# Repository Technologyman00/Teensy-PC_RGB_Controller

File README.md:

# Teensy-PC_RGB_Controller
 
The whole Idea behind this project was to create a much better RGB controller than the controllers or motherboard software I have seen. Currently It has already met that goal as it can play any pattern for many LEDs and up to individual 40 devices. I am still working on the user interface and many qualities of life things, but the main functionality does work. HOWEVER, it will need a PCB made to power all the LEDs as a Teensy cannot power that many safely.

## Features

- No Extra load on the CPU. The teensy has its own built in CPU that will handle all the commands to the ARGB devices.
- Store Loads of Patterns or Huge animations. The teensy uses an SD card to save and read all the patterns allowing for a huge number of patterns to be saved.
- Up to 40 ports. Most Controllers top out at a maximum of 4 ports. The teensy has 40! This allows each device to do its own individual pattern.
- Any pattern! There are no limitations on what can be displayed because it plays back frames allowing an almost infinite amount of customization. 
- Standard Plugs! This uses the regular 3 pin 5V ARGB connectors so any device with the same connector can be used!
- OPEN SOURCE! Are you a bit handier than most? You can change anything you would ever what about this project!

## Documentation
### Pattern Files

Description | Command | Argument 1 | Argument 2
------------ | -------------| ------------ | -------------|
Send RGB Command: | 0 | Port Number | Color Data |
Send HSV Command: | 1 | Port Number | Hue (2 Bytes) S (1 Byte) V (1 Byte)|
Change Frame Delay: | 2 | Delay (2 Bytes) | N/A |
Create Device/Change Length: | 3 | Port Number | Number of Pixels |
Start New Frame: | 4 | N/A | N/A | N/A |

- Port 13 is not accessable from the hardware as it has the status LED so it was intentionally skipped in the PCB design. 

- Color Data is a continuous set of the RGB or HSV values. It will be (3 * Number of Pixels in Device) bytes long. For example it would go (Red Byte)(Blue Byte)(Green Byte)(Red Byte)(Blue Byte)(Green Byte)... or (Hue Byte)(Saturation Byte)(Value Byte)(Hue Byte)(Saturation Byte)(Value Byte)... All these bytes are from 0-255 with no decimals, as bytes are. For hue, saturation, and value these are all scaled to their corrective values.

- The delay value is split into 2 different bytes to allow a delay between 0 and 65535ms or 65.5 seconds. This allows a great range between quick animations and still colors. This value does not matter so much for still colors as the pattern file will just start over once it reaches the end re-displaying the same color.

### Serial Commands

Description | Command | Argument 1 | Argument 2 | Argument 3 |
------------ | -------------| ------------ | -------------| -------------|
Play File on SD Card: | P | File Name | N/A | N/A |
Write File to SD Card: | W | File Name | Length to Read (4 Bytes) | File Data |
Delete File on SD Card: | X | File Name | N/A | N/A |
List Files on SD Card: | L | N/A | N/A | N/A |
Change Startup File: | S | File Name | N/A | N/A |
Display Frame: | D | RGB or HSV -> (0 or 1) | Port Number | Color Data |
New Device: | N | Port | Number of Pixels | N/A |
Restart Teensy: | R | N/A | N/A | N/A |
Check Teensy Tempature: | T | N/A | N/A | N/A |

- File Name requires the file type *"example.txt"*
- File Data follows the documentation as setup in pattern files
- Length to Read is split into 4 bytes to allow very large files to be transferred (~4.3 GB) (if larger than ~4.3 GB just put the file onto the SD card manually)
- Color Data also follows the documentation as shown in pattern files
- ***Deleting files will ask if "Are sure you want to delete this?" A response is needed of Y/N before it will continue. Everything is halted when this is prompted.***
- ***Showing a Frame will not return to normal file reading until an exit command of X is sent.***

### Startup Handler

On startup the teensy will first read the *startup.txt* file which should contain the name of the file and only the name of the file. If this file does not exist or the code is unhappy with what was entered it will delete the *startup.txt* file and replace it with a *startup.txt* file that will run the default pattern file. The default pattern file sets all 40 ports to display Green on 255 pixels on those ports. This should make it so that it is obvious that the Teensy is working. The *startup.txt* file can be changed by either editing the file in a text editor or by sending the S command over serial.

## Updates
6/6
Full Deployment!!!!!
Example 1: https://youtu.be/utrNA2Hu2Kg
Example 2: https://youtu.be/6SqUPKUgLiA

5/30 Version 2 of the PCB was ordered and should be arriving shortly. This new version is to fix the concerns with the previous version, as the size was quite large and there was a design error. Both should be fixed in this version. Pin 13 was also taken off of the available pins as it was decided that it should be used as a status LED and should remain off if used. 

3/14 PCB Came in had issues. The Output enable pin was grounded not powered, which means it was disabled not enabled. (Woops) A small soldered wire fixed that. 
First Test : https://youtu.be/IeGvDfm8C_M

## Limitations
#### Files
   - Limited to a File Name of 8 Characters
     - example1.txt is at the max length
   - Is not case-sensitive 
     - example1.txt == EXAMPLE1.txt
      
#### Max SD card size is 32 GB
   - There are some potential work arounds for larger SD cards
   
#### LED Devices can only be added not removed per a given reboot
   - I really cant imagine this being an issue for anyone, but I thought its important to note just incase.
   - If 40 devices are created then they cannot be removed until a reboot
   - All 40 devices will be written to until a reboot occurs

## To Do
- [ ] Create Pattern Designer
- [ ] Loop Commands inside Files?
- [ ] Command Files for other Files?
- [ ] Allow devices to be removed without reboot?

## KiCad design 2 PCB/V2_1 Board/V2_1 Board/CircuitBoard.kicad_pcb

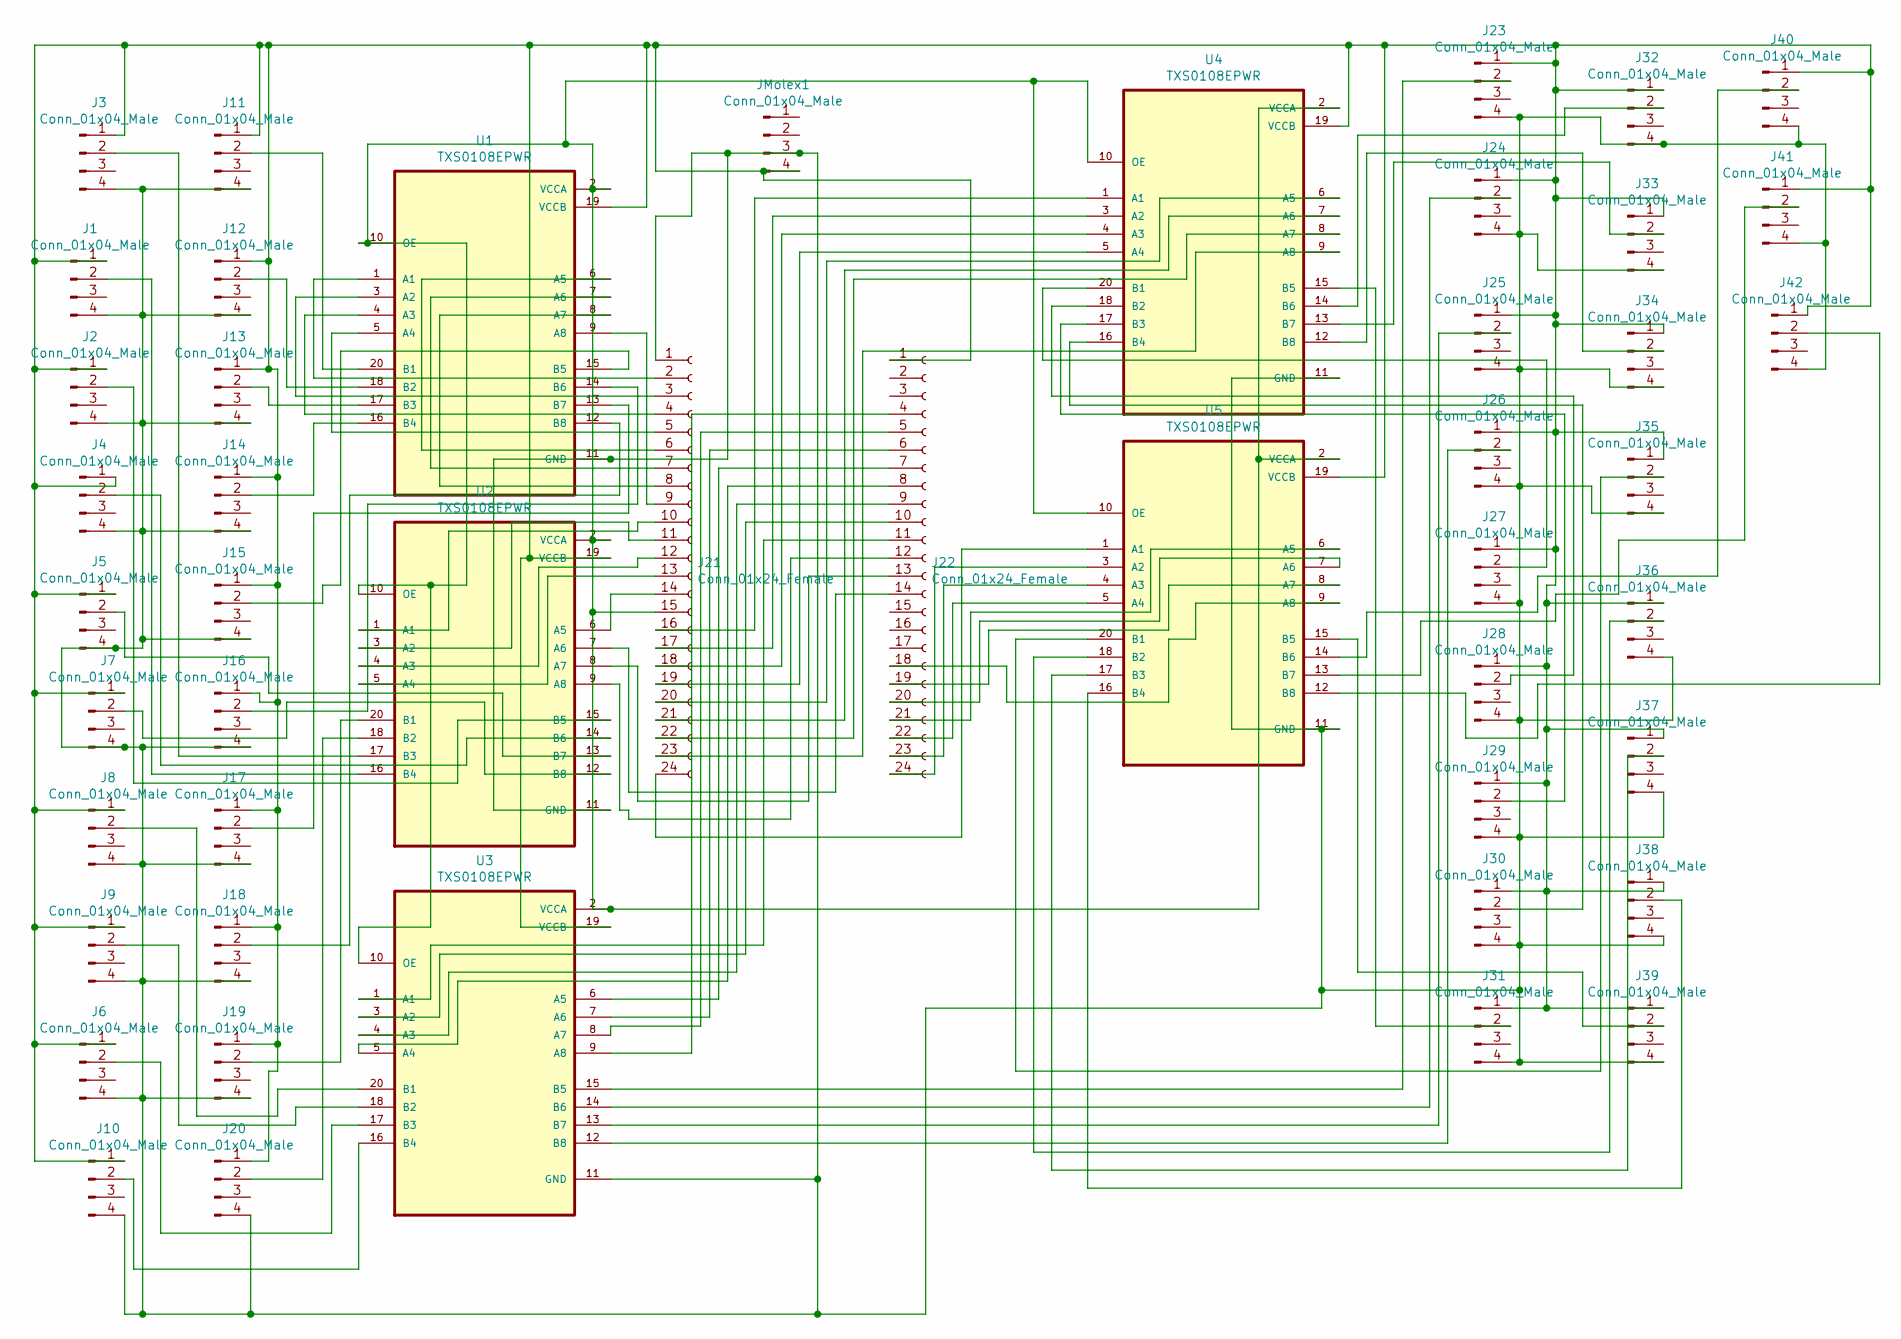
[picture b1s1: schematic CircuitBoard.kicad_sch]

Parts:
J1, J2, J3, J4, J5, J6, J7, J8, J9, J10, J11, J12, J13, J14, J15, J16, J17, J18, J19, J20, J23, J24, J25, J26, J27, J28, J29, J30, J31, J32, J33, J34, J35, J36, J37, J38, J39, J40, J41, J42: Conn_01x04_Male; FanPinHeader_1x04_P2.54mm_Vertical
J21, J22: Conn_01x24_Female; PinSocket_1x24_P2.54mm_Vertical
JMolex1: Conn_01x04_Male; 7708461
U1, U2, U3, U4, U5: TXS0108EPWR; SOP65P640X120-20N

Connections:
unnamed: J1.2, U2.16 (B4)
unnamed: J1.4, J2.4, J3.4, J4.4, J5.4, J6.4, J7.4, J8.4, J9.4, J10.4, J11.4, J12.4, J13.4, J14.4, J15.4, J16.4, J17.4, J18.4, J19.4, J20.4, J21.1, J23.4, J24.4, J25.4, J26.4, J27.4, J28.4, J29.4, J30.4, J31.4, J32.4, J33.4, J34.4, J35.4, J36.4, J37.4, J38.4, J39.4, J40.4, J41.4, J42.4, JMolex1.3, U1.11 (GND), U2.11 (GND), U3.11 (GND), U4.11 (GND), U5.11 (GND)
unnamed: J2.2, U2.15 (B5)
unnamed: J3.2, U2.17 (B3)
unnamed: J4.2, U2.14 (B6)
unnamed: J5.2, U2.13 (B7)
unnamed: J6.2, U3.17 (B3)
unnamed: J7.2, U2.12 (B8)
unnamed: J8.2, U3.20 (B1)
unnamed: J9.2, U3.18 (B2)
unnamed: J10.2, U3.16 (B4)
unnamed: J11.2, U1.20 (B1)
unnamed: J12.2, U1.18 (B2)
unnamed: J13.2, U1.17 (B3)
unnamed: J14.2, U1.16 (B4)
unnamed: J15.2, U1.15 (B5)
unnamed: J16.2, U1.14 (B6)
unnamed: J17.2, U1.13 (B7)
unnamed: J18.2, U1.12 (B8)
unnamed: J19.2, U2.20 (B1)
unnamed: J20.2, U2.18 (B2)
unnamed: J21.2, U1.1 (A1)
unnamed: J21.3, U1.3 (A2)
unnamed: J21.4, U1.4 (A3)
unnamed: J21.5, U1.5 (A4)
unnamed: J21.6, U1.6 (A5)
unnamed: J21.7, U1.7 (A6)
unnamed: J21.8, U1.8 (A7)
unnamed: J21.9, U1.9 (A8)
unnamed: J21.10, U2.1 (A1)
unnamed: J21.11, U2.3 (A2)
unnamed: J21.12, U2.4 (A3)
unnamed: J21.13, U2.5 (A4)
unnamed: J21.14, U2.6 (A5)
unnamed: J21.15, U1.2 (VCCA), U1.10 (OE), U2.2 (VCCA), U2.10 (OE), U3.2 (VCCA), U3.10 (OE), U4.2 (VCCA), U4.10 (OE), U5.2 (VCCA), U5.10 (OE)
unnamed: J21.16, U4.1 (A1)
unnamed: J21.17, U4.3 (A2)
unnamed: J21.18, U4.4 (A3)
unnamed: J21.19, U4.5 (A4)
unnamed: J21.20, U4.6 (A5)
unnamed: J21.21, U4.7 (A6)
unnamed: J21.22, U4.8 (A7)
unnamed: J21.23, U4.9 (A8)
unnamed: J21.24, U5.1 (A1)
unnamed: J22.4, U3.9 (A8)
unnamed: J22.5, U3.8 (A7)
unnamed: J22.6, U3.7 (A6)
unnamed: J22.7, U3.6 (A5)
unnamed: J22.8, U3.5 (A4)
unnamed: J22.9, U3.4 (A3)
unnamed: J22.10, U3.3 (A2)
unnamed: J22.11, U3.1 (A1)
unnamed: J22.12, U2.9 (A8)
unnamed: J22.13, U2.8 (A7)
unnamed: J22.14, U2.7 (A6)
unnamed: J22.18, U5.9 (A8)
unnamed: J22.19, U5.8 (A7)
unnamed: J22.20, U5.7 (A6)
unnamed: J22.21, U5.6 (A5)
unnamed: J22.22, U5.5 (A4)
unnamed: J22.23, U5.4 (A3)
unnamed: J22.24, U5.3 (A2)
unnamed: J23.2, U3.15 (B5)
unnamed: J24.2, U3.14 (B6)
unnamed: J25.2, U3.13 (B7)
unnamed: J26.2, U3.12 (B8)
unnamed: J27.2, U4.20 (B1)
unnamed: J28.2, U4.18 (B2)
unnamed: J29.2, U4.17 (B3)
unnamed: J30.2, U4.16 (B4)
unnamed: J31.2, U4.15 (B5)
unnamed: J32.2, U4.14 (B6)
unnamed: J33.2, U4.13 (B7)
unnamed: J34.2, U4.12 (B8)
unnamed: J35.2, U5.20 (B1)
unnamed: J36.2, U5.18 (B2)
unnamed: J37.2, U5.17 (B3)
unnamed: J38.2, U5.16 (B4)
unnamed: J39.2, U5.15 (B5)
unnamed: J40.2, U5.14 (B6)
unnamed: J41.2, U5.13 (B7)
unnamed: J42.2, U5.12 (B8)

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
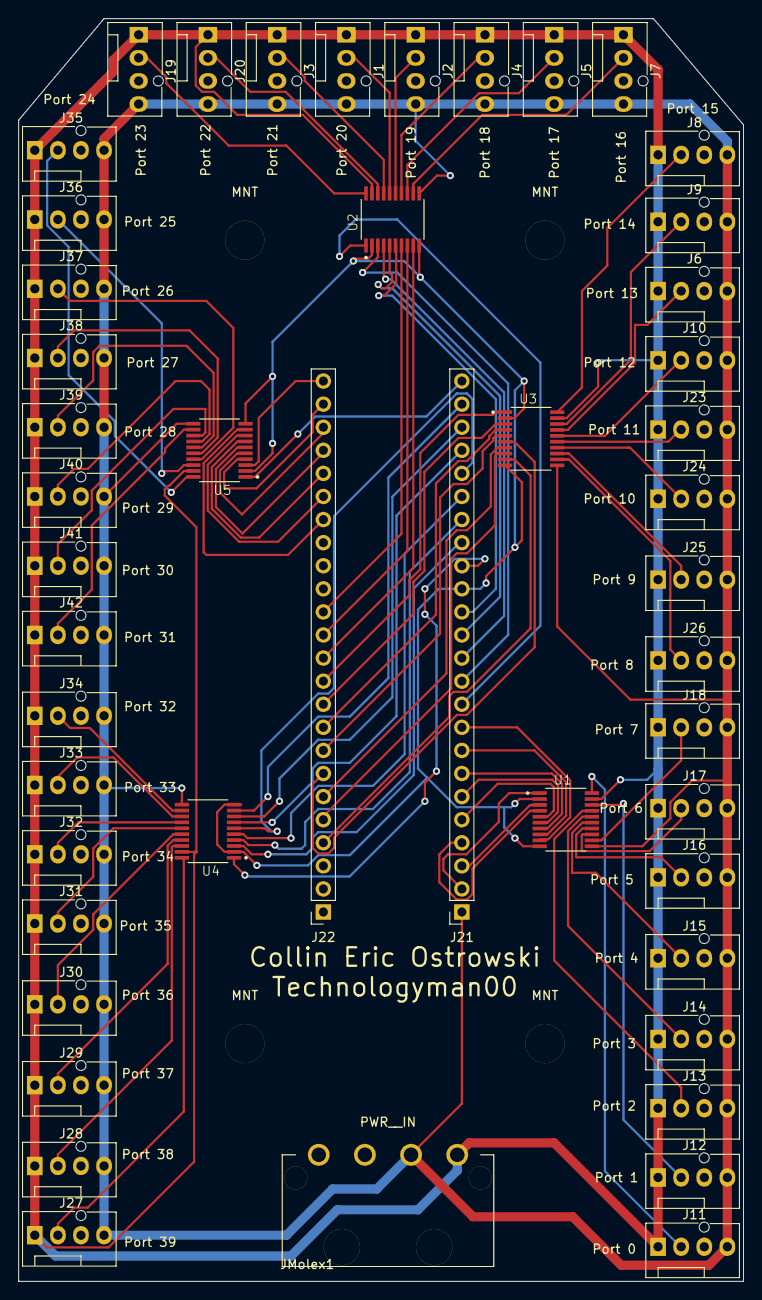
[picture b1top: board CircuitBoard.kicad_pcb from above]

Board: 2 copper layers, 79.8 x 138.9 mm, 52 parts (0 on the bottom side), 83 nets.

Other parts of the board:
MNT: MountingHole_4.3mm_M4
MNT#2, MNT#3, MNT#4: MountingHole_4.3mm_M4

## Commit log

2020-12-21 Inital Push
    Brings all the new and old stuff to github
2020-12-21 Reorganized Files
2020-12-21 Writing File over Serial Added but not working
    Writing File over Serial Added but not working. Seems to crash after creating the file because if tried to create the same file name it will cause it to alert properly to saying the file already exis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
2020-12-21 Added Project Description
2020-12-23 Updated Info
2020-12-23 Fixing Some Serial Issues
2020-12-23 First Attempt at VSCode Transfer
2020-12-23 VSCode Transfer Complete
    Arduino's IDE was getting crouded and annoying, so moving to VSCode for a better IDE and to help with easier Multi-file coding. It also makes C++ a bit more true to form instead of the Arduino flavor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
2020-12-24 Added Live Frame Sending
    Live Frame Sending added for displaying temp. It does not work 100% properly yet.
2020-12-24 Changed how Delaying between frames works
    Old Delays used to just delay between frames. This is bad because if told to delay for a long time then serial commands wont work until after delay has happend. Which will be really really really bad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
2020-12-25 Added Restart ability to Teensy and Started work on Desktop Apps
    The Teensy can now be restarted with the serial command "r" and there is now an .exe for sending this command. It does only work for it being on COM4 however. This will need to be updated.
2020-12-25 Changed Startup behavoir
    The Teensy will now create a startup.txt where it will store the name of the file to play when it starts up. If that file does not exist it will create it and create a default pattern to play.
2020-12-25 Cleaned Up Default File Code and Added Startup File Changing command.
    The code for creating the default file and startup file was a bit messy, so that was cleaned up. A command to change which file is run on startup was also added. "s (file name to run)"
2020-12-26 Bug Fixes and More Desktop App Features
    Fixed some bugs with switching to a different file to play and fixed a bug where issues with the startup file would not cause the default file to play. The desktop apps can now send commands to play 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
2020-12-26 Added Documentation
2020-12-26 Added Features display
2020-12-26 Added creating new devices over serial and now allows any case for Serial commands
2020-12-27 Fixed Cpp Sending File Exe
2020-12-27 Added FindTeensy.exe
    Created a program to find the connected teensy. This will be incorperated into the other programs for sending data to the teensy.
2020-12-29 Work Done on PCB and Added Automatic Port Finding
    Work Done on PCB. It is pretty terrible, but it is being reviewed by a EE friend of mine. Added Automatic Port Finding, for the very likely chance the teensy isnt on COM4
2020-12-29 Completed More
2020-12-29 Start of Pattern Creator
    Mainly Testing out the github pages feature for hosting the webpage for pattern creation.
2020-12-29 Set theme jekyll-theme-cayman
2020-12-29 Alerting location of pattern creator
2021-01-01 Added Parallel LEDs Commands and worked on Circuit Board
    Parallel LED Commands allow for sigificantly faster data sending to LEDs and Circuit board is mostly finalized and was reviewed and confirmed to be good.
2021-01-01 Added and Finished More To Dos
2021-01-03 Fixed how Includes are managed
    Changed includes to only import OctoWS2811 for parallel and only FastLED for non parallel.
2021-03-14 Production PCB Added
    Production PCB Added it was noticed since prodution there is an issue with the PCB that needs to be addressed in a future update. For now it can be fixed mostly by ripping the resistor off the board.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
2021-03-21 PCB fix
2021-05-31 Updates for new progress
2021-05-31 PCB V2 & Case Work & Code Updates
    PCB Version 2 started and completed. This makes it smaller and should fix the issues with having to solder a patch wire to the board. It also makes pin 13 no longer used for controlling the connected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
2021-06-07 New Patterns and New Features and Deployment
    Some changes as it was fully deployed and I was able to test everything. I was concerned about the temperature of the teensy so I added another serial command to check the internal temperature of the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
2021-06-08 New Patterns and Deleted Gcode
2021-06-09 New Patterns
2021-12-15 Documentation Changes for Future Update
2021-12-15 Hue resolution changed to two bytes
    Hue resolution changed to two bytes. I wasn't happy how obvious it was when the color changed for hue, so I made it 2 bytes for significantly higher resolution. I also recently got some RGB ram, so I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
2021-12-19 Rainbow Pattern Done
    Rainbow Pattern Done. Finally!
